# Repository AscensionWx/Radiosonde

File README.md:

# Radiosonde
Collection of tools for DIY Weather Balloons and Forecasting

For Kanda Weather (Africa) and AscensionWx (U.S.), and open under MIT license.

|  TTGO LoRa32 v2.1     |     Cybaart Kanda Aeolus   |     KandaWeather Launch 
:-------------------------:|:-------------------------:|:-------------------------:
|   |   |   |

Components:
- Hardware
- 3d print files
- Firmware
- LoRaWAN decoders
- Node-red flow files
- Blockchain Smart contract

- Forecasting Dashboard
- Machine Learning Datasets

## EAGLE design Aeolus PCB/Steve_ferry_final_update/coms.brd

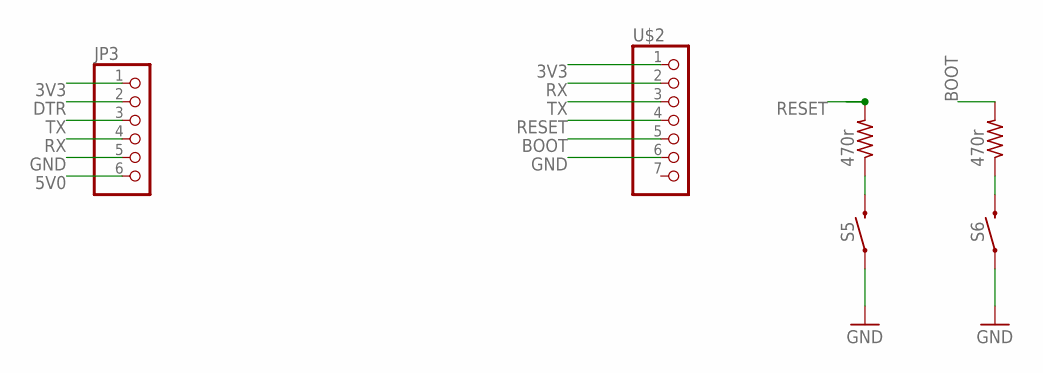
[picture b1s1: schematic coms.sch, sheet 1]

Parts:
JP3: HEADER-1X6ROUND; 1X06_ROUND
R5, R6: 470r; M1206
S5, S6: MOMENTARY-SWITCH-SPST; TACTILE_SWITCH_C480275
U$2: HEADER-1X7ROUND; 1X07_ROUND

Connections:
3V3: JP3.1, U$2.1; also elsewhere on the board
5V0: JP3.6; also elsewhere on the board
BOOT: R6.2, U$2.5; also elsewhere on the board
DTR: JP3.2; also elsewhere on the board
GND: JP3.5, S5.1, S5.2 (1), S6.1, S6.2 (1), U$2.6; also elsewhere on the board
unnamed: R5.1, S5.3 (2), S5.4 (2)
unnamed: R6.1, S6.3 (2), S6.4 (2)
RESET: R5.2, U$2.4; also elsewhere on the board
RX: JP3.4, U$2.2; also elsewhere on the board
TX: JP3.3, U$2.3; also elsewhere on the board

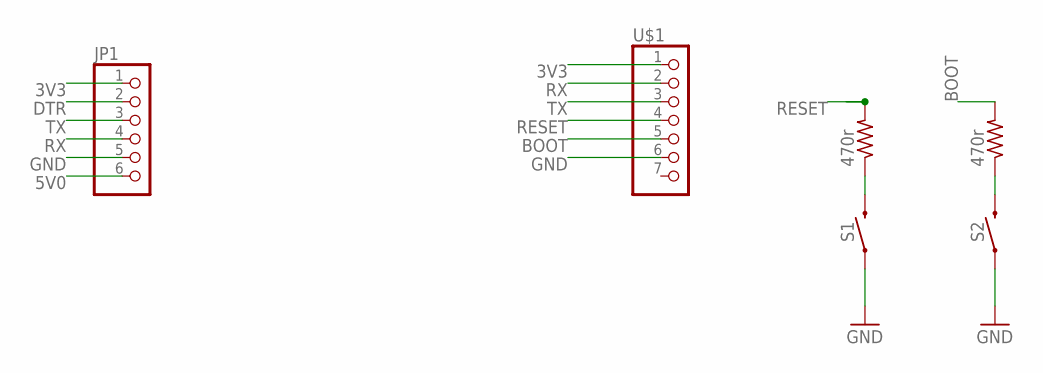
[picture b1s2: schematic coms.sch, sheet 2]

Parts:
JP1: HEADER-1X6ROUND; 1X06_ROUND
R1, R2: 470r; M1206
S1, S2: MOMENTARY-SWITCH-SPST; TACTILE_SWITCH_C480275
U$1: HEADER-1X7ROUND; 1X07_ROUND

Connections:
3V3: JP1.1, U$1.1; also elsewhere on the board
5V0: JP1.6; also elsewhere on the board
BOOT: R2.2, U$1.5; also elsewhere on the board
DTR: JP1.2; also elsewhere on the board
GND: JP1.5, S1.1, S1.2 (1), S2.1, S2.2 (1), U$1.6; also elsewhere on the board
unnamed: R1.1, S1.3 (2), S1.4 (2)
unnamed: R2.1, S2.3 (2), S2.4 (2)
RESET: R1.2, U$1.4; also elsewhere on the board
RX: JP1.4, U$1.2; also elsewhere on the board
TX: JP1.3, U$1.3; also elsewhere on the board

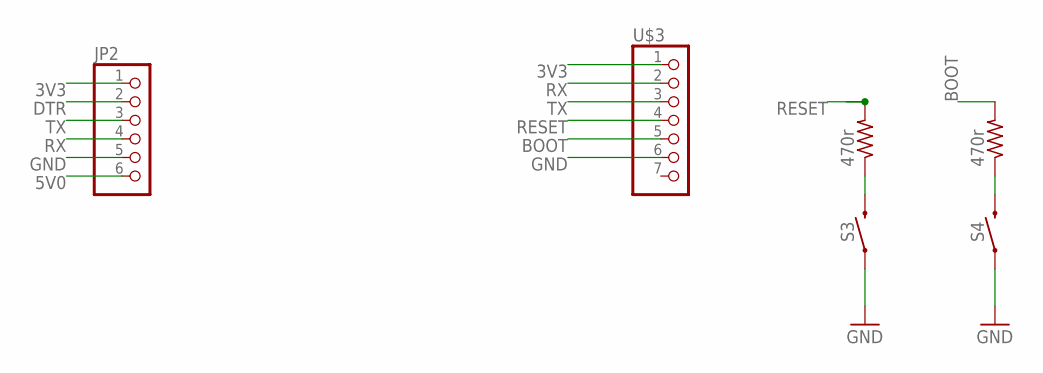
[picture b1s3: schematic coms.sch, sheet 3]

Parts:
JP2: HEADER-1X6ROUND; 1X06_ROUND
R3, R4: 470r; M1206
S3, S4: MOMENTARY-SWITCH-SPST; TACTILE_SWITCH_C480275
U$3: HEADER-1X7ROUND; 1X07_ROUND

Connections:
3V3: JP2.1, U$3.1; also elsewhere on the board
5V0: JP2.6; also elsewhere on the board
BOOT: R4.2, U$3.5; also elsewhere on the board
DTR: JP2.2; also elsewhere on the board
GND: JP2.5, S3.1, S3.2 (1), S4.1, S4.2 (1), U$3.6; also elsewhere on the board
unnamed: R3.1, S3.3 (2), S3.4 (2)
unnamed: R4.1, S4.3 (2), S4.4 (2)
RESET: R3.2, U$3.4; also elsewhere on the board
RX: JP2.4, U$3.2; also elsewhere on the board
TX: JP2.3, U$3.3; also elsewhere on the board

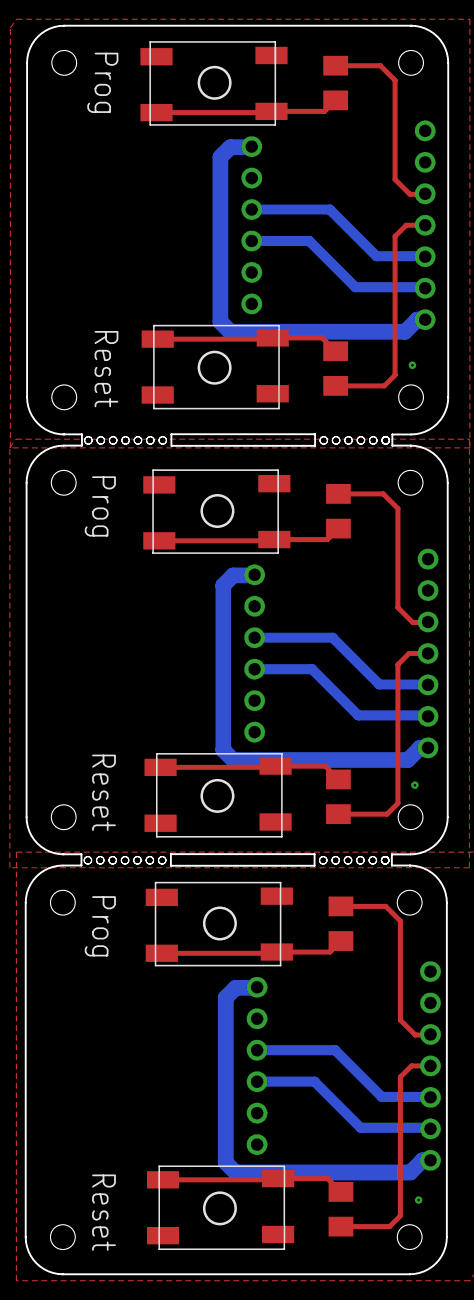
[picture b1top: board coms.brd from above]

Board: 2 copper layers, 34.1 x 100.8 mm, 18 parts (0 on the bottom side), 14 nets.

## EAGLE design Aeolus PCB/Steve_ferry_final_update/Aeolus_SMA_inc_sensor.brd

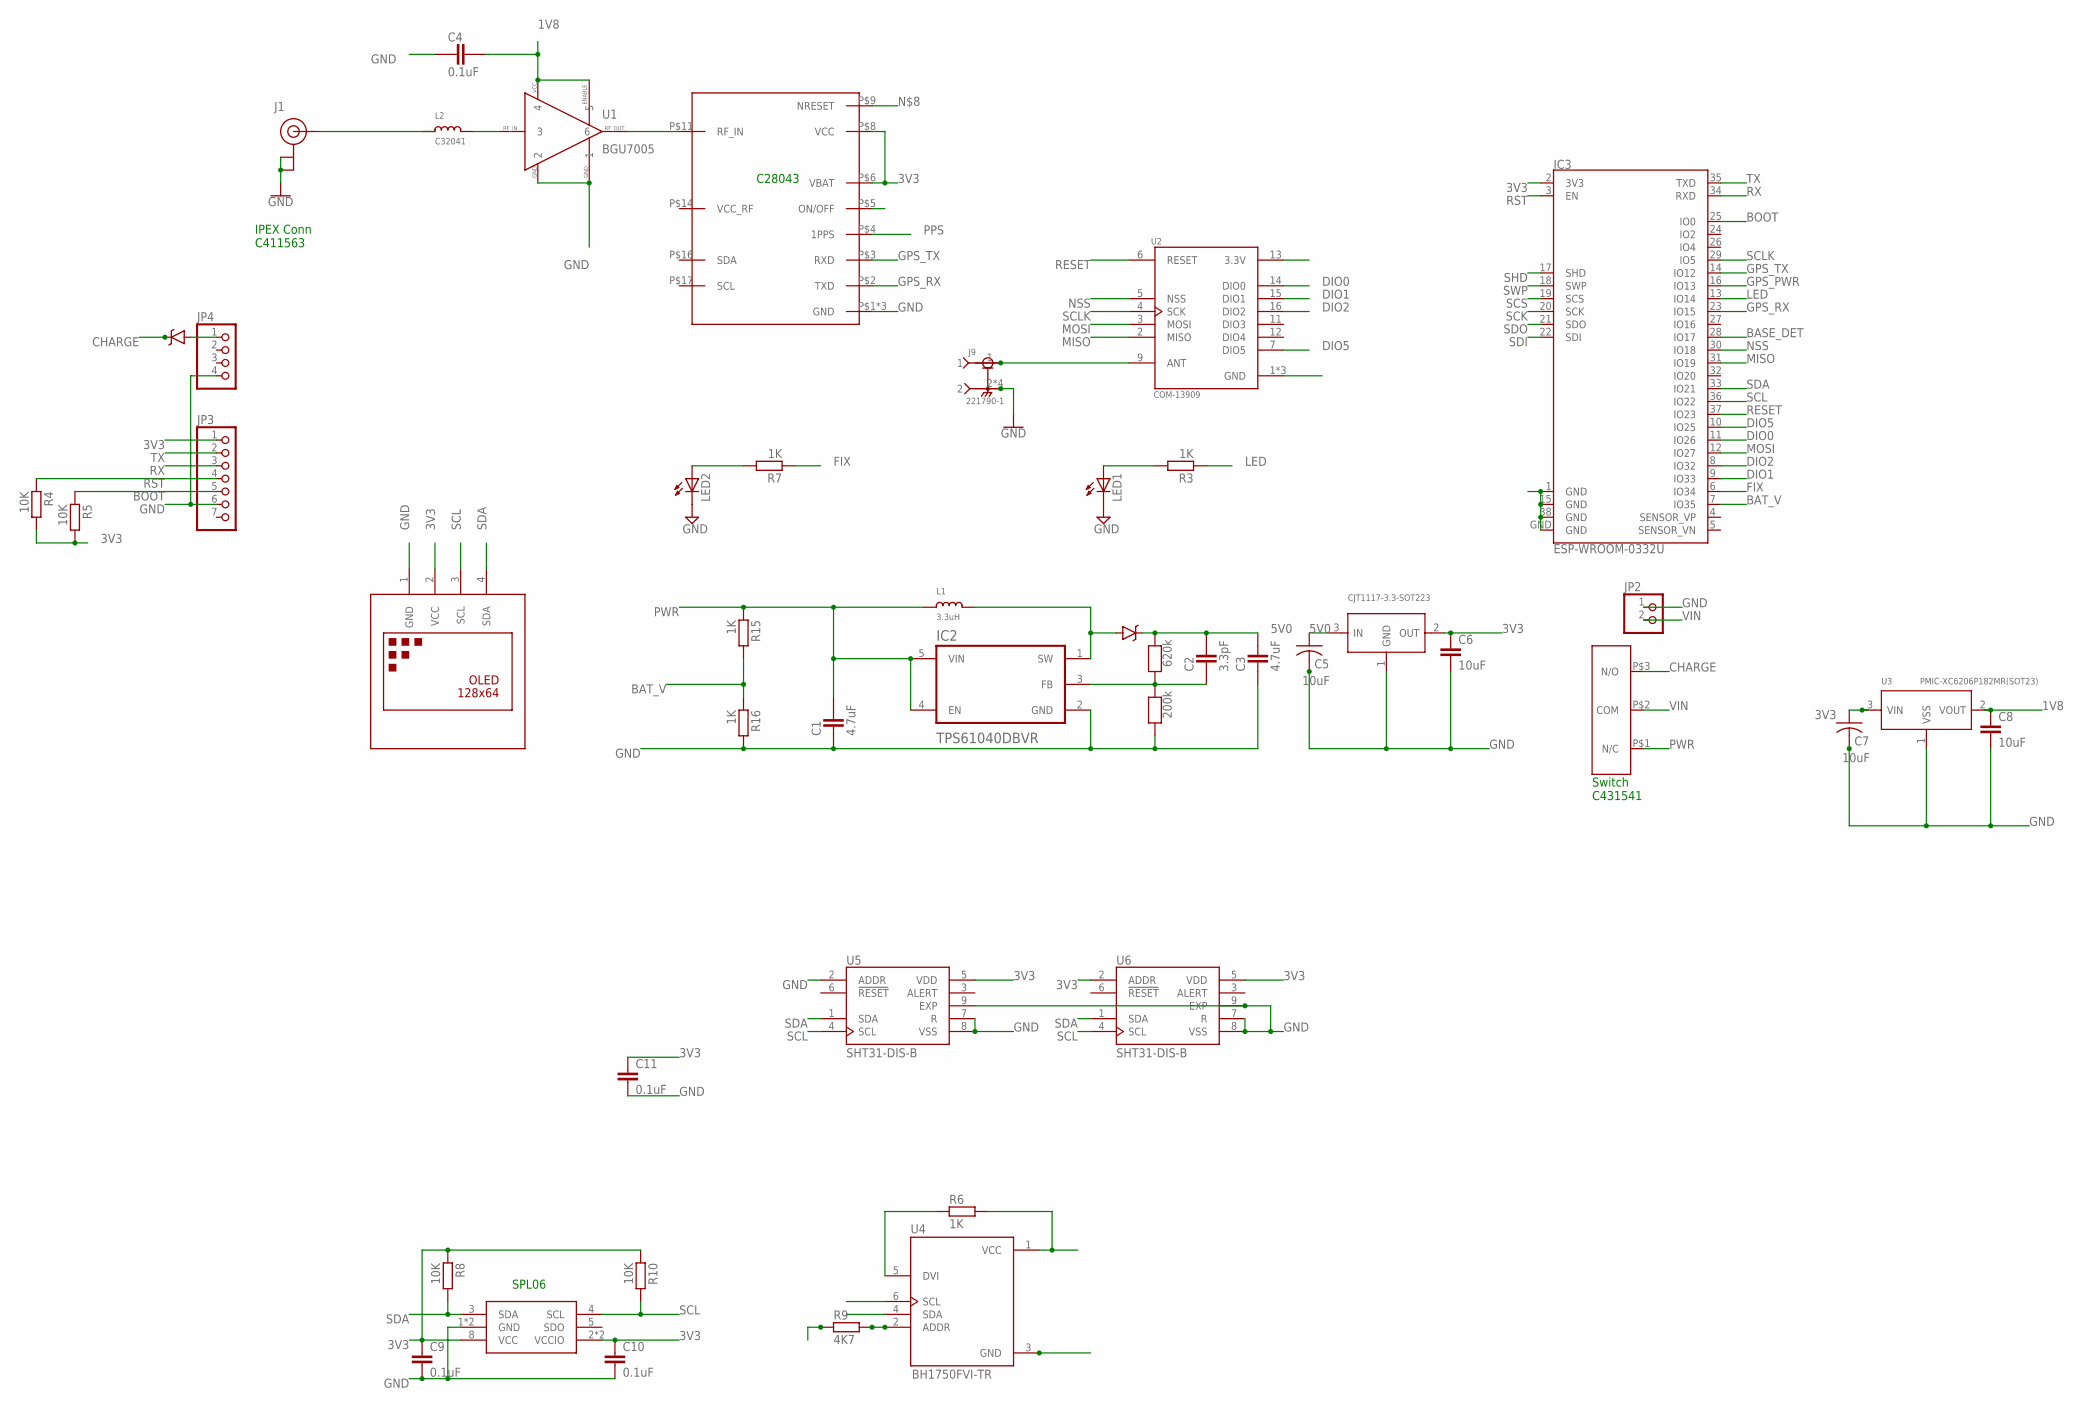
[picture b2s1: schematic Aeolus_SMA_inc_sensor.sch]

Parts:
C1, C3: 4.7uF; CAPC1608X92N
C2: 3.3pF; CAPC1005X60N
C4: 0.1uF; CAPC1608X92N
C5: 10uF; C0805
C6: 10uF; C0805@1
C7: 10uF; C0402
C8: 10uF; C0402K@1
C9, C10, C11: 0.1uF; C0603@1
D1, D2: BA340A; SMA-DIODE
IC1: CJT1117-3.3-SOT223; SOT-223
IC2: TPS61040DBVR; SOT95P280X145-5N
IC3: ESP-WROOM-0332U; ESP32-WROOM-32U
IC54: ATGM336H
J1: U.FL
J9: 221790-1; TE_221790-1
JP2: HEADER-1X2ROUND; 1X02_ROUND
JP3: HEADER-1X7ROUND; 1X07_ROUND
JP4: HEADER-1X4ROUND; 1X04_ROUND
L1: 3.3uH; INDUCTOR_5X5MM_NR5040_NOTHERMALS
L2: C32041; _0402
LED1, LED2: LEDSML0805; SML0805
R1: 620k; 0603
R2: 200k; 0603
R3, R6, R7, R15, R16: 1K; RESC1608X55N
R4, R5, R8, R10: 10K; RESC1608X55N
R9: 4K7; RESC1608X55N
S1: SMD-SWITCH
U1: BGU7005; SOT886
U2: COM-13909; MOD_COM-13909
U3: PMIC-XC6206P182MR(SOT23); SOT-23
U4: BH1750FVI-TR; XDCR_BH1750FVI-TR
U5, U6: SHT31-DIS-B; SON50P250X250X100-9N
U$1: DISPLAY-OLED-128X64-I2C
U$4: SPL06

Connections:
1V8: C4.2, C8.1, U1.4, U1.5, U3.2 (VOUT)
3V3: C6.1, C7.1, C9.1, C10.1, C11.1, IC1.2 (OUT), IC3.2 (3V3), IC54.P$6 (VBAT), IC54.P$8 (VCC), JP3.1, R4.2, R5.2, R6.2, R8.1, R10.1, U2.13 (3.3V), U3.3 (VIN), U4.1 (VCC), U5.5 (VDD), U6.2 (ADDR), U6.5 (VDD), U$1.2 (VCC), U$4.2 (VCCIO), U$4.6 (VCCIO), U$4.8 (VCC)
5V0: C2.2, C3.2, C5.1, D1.C, IC1.3 (IN), R1.1
ANT: J9.1, U2.9 (ANT)
BASE_DET: IC3.28 (IO17)
BAT_V: IC3.7 (IO35), R15.2, R16.1
BOOT: IC3.25 (IO0), JP3.5, R5.1
CHARGE: D2.C, S1.P$3 (N/O)
DIO0: IC3.11 (IO26), U2.14 (DIO0)
DIO1: IC3.9 (IO33), U2.15 (DIO1)
DIO2: IC3.8 (IO32), U2.16 (DIO2)
DIO5: IC3.10 (IO25), U2.7 (DIO5)
FB: C2.1, IC2.3 (FB), R1.2, R2.1
FIX: IC3.6 (IO34), R7.1
GND: C1.1, C3.1, C4.1, C5.2, C6.2, C7.2, C8.2, C9.2, C10.2, C11.2, IC1.1 (GND), IC2.2 (GND), IC3.1 (GND), IC3.15 (GND), IC3.38 (GND), IC3.GND, IC54.P$1 (GND), IC54.P$10 (GND), IC54.P$12 (GND), J1.1 (GND), J1.2 (GND), J9.2, J9.3 (2), J9.4 (2), J9.5 (2), JP2.1, JP3.6, JP4.4, LED1.C, LED2.C, R2.2, R9.1, R16.2, U1.1, U1.2, U2.1 (GND), U2.8 (GND), U2.10 (GND), U3.1 (VSS), U4.3 (GND), U5.2 (ADDR), U5.7 (R), U5.8 (VSS), U5.9 (EXP), U6.7 (R), U6.8 (VSS), U6.9 (EXP), U$1.1 (GND), U$4.1 (GND), U$4.7 (GND)
GPS_PWR: IC3.16 (IO13)
GPS_RX: IC3.23 (IO15), IC54.P$2 (TXD)
GPS_TX: IC3.14 (IO12), IC54.P$3 (RXD)
LED: IC3.13 (IO14), R3.1
MISO: IC3.31 (IO19), U2.2 (MISO)
MOSI: IC3.12 (IO27), U2.3 (MOSI)
unnamed: D1.A, IC2.1 (SW), L1.P$2 (2)
unnamed: D2.A, JP4.1
unnamed: LED1.A, R3.2
unnamed: J1.FEED (SIGNAL), L2.1
unnamed: LED2.A, R7.2
unnamed: IC54.P$11 (RF_IN), U1.6
unnamed: R6.1, U4.5 (DVI)
unnamed: L2.2, U1.3
unnamed: R9.2, U4.2 (ADDR)
NSS: IC3.30 (IO18), U2.5 (NSS)
PPS: IC54.P$4 (1PPS)
PWR: C1.2, IC2.4 (EN), IC2.5 (VIN), L1.P$1 (1), R15.1, S1.P$1 (N/C)
RESET: IC3.37 (IO23), U2.6 (RESET)
RST: IC3.3 (EN), JP3.4, R4.1
RX: IC3.34 (RXD), JP3.3
SCK: IC3.20 (SCK)
SCL: IC3.36 (IO22), R10.2, U4.6 (SCL), U5.4 (SCL), U6.4 (SCL), U$1.3 (SCL), U$4.4 (SCL)
SCLK: IC3.29 (IO5), U2.4 (SCK)
SCS: IC3.19 (SCS)
SDA: IC3.33 (IO21), R8.2, U4.4 (SDA), U5.1 (SDA), U6.1 (SDA), U$1.4 (SDA), U$4.3 (SDA)
SDI: IC3.22 (SDI)
SDO: IC3.21 (SDO)
SHD: IC3.17 (SHD)
SWP: IC3.18 (SWP)
TX: IC3.35 (TXD), JP3.2
VIN: JP2.2, S1.P$2 (COM)

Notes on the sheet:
Switch C431541
IPEX Conn C411563
C28043
SPL06

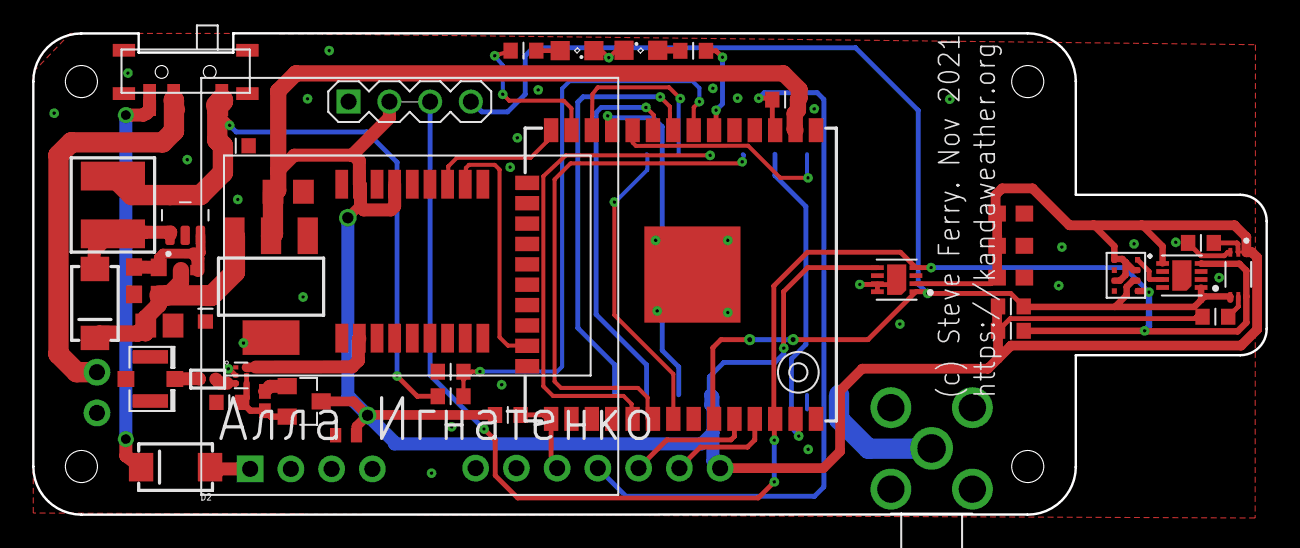
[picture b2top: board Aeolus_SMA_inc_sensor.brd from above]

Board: 2 copper layers, 76.9 x 30.0 mm, 47 parts (1 on the bottom side), 38 nets.

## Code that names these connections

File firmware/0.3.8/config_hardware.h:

#define DEBUG_PORT              Serial      // Serial debug port
#define SERIAL_BAUD             115200      // Serial debug baud rate

#ifdef DEBUG_PORT
#define DEBUG_MSG(...) DEBUG_PORT.printf( __VA_ARGS__ )
#else
#define DEBUG_MSG(...)
#endif

// -----------------------------------------------------------------------------
// General
// -----------------------------------------------------------------------------

#define I2C_SDA         21
#define I2C_SCL         22
#define LED_PIN         14
#define RELAIS_PIN         14   // Works with TTGO LoRa32 V2.1 board (confirmed)
#define BUTTON_PIN      39

// -----------------------------------------------------------------------------
// OLED
// -----------------------------------------------------------------------------

#define SSD1306_ADDRESS 0x3C

// -----------------------------------------------------------------------------
// T, Pressure, Humidity
// -----------------------------------------------------------------------------

#define BME280_ADDRESS_0x76 0x76
#define BME280_ADDRESS_0x77 0x77
#define SPL06_ADDRESS_0x76 0x76
#define SPL06_ADDRESS_0x77 0x77
#define SHT21_ADDRESS 0x40

// -----------------------------------------------------------------------------
// GPS
// -----------------------------------------------------------------------------

#define GPS_BAUDRATE    9600
#define USE_GPS         1
#define ss              Serial2 // define GPSserial as ESP32 Serial2
#define LMIC_WAIT       3000 // The lmic library requires minimum of 2.7 seconds to complete RX2 (maybe more if SF10 to SF12)
#define GPS_WAIT        1900 // Should be longer than 1 second (default on GPS)

// Options on ESP32 are:
//   RX: 3   TX: 1    == Serial0
//   RX: 9   TX: 10   == Serial1
//   RX: 16  TX: 17   == Serial2

#define GPS_RX_PIN      1
#define GPS_TX_PIN      3
#define GPS_POWER_PIN   AXP192_LDO3

// -----------------------------------------------------------------------------
// LoRa SPI
// -----------------------------------------------------------------------------

#define SCK_GPIO        5
#define MISO_GPIO       19
#define MOSI_GPIO       27
#define NSS_GPIO        18
#define RESET_GPIO      23
#define DIO0_GPIO       26
#define DIO1_GPIO       33
#define DIO2_GPIO       32

#define CLOCK_ERROR             1

// -----------------------------------------------------------------------------
// AXP192 (Rev1-specific options)
// -----------------------------------------------------------------------------

#define AXP192_SLAVE_ADDRESS  0x34
#define GPS_POWER_CTRL_CH     3
#define LORA_POWER_CTRL_CH    2
#define PMU_IRQ               35

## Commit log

2023-05-15 Add MIT License
2023-05-20 Add pictures
2023-08-03 Create credentials.h
    Dummy credentials file. Edit prior to deploying

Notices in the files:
parts and their libraries:
microbuilder: This work is placed in the public domain, and may be freely used for commercial and non-commercial work with the following conditions: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
diy-modules: Released under the Creative Commons Attribution 4.0 International License: http://creativecommons.org/licenses/by/4.0
